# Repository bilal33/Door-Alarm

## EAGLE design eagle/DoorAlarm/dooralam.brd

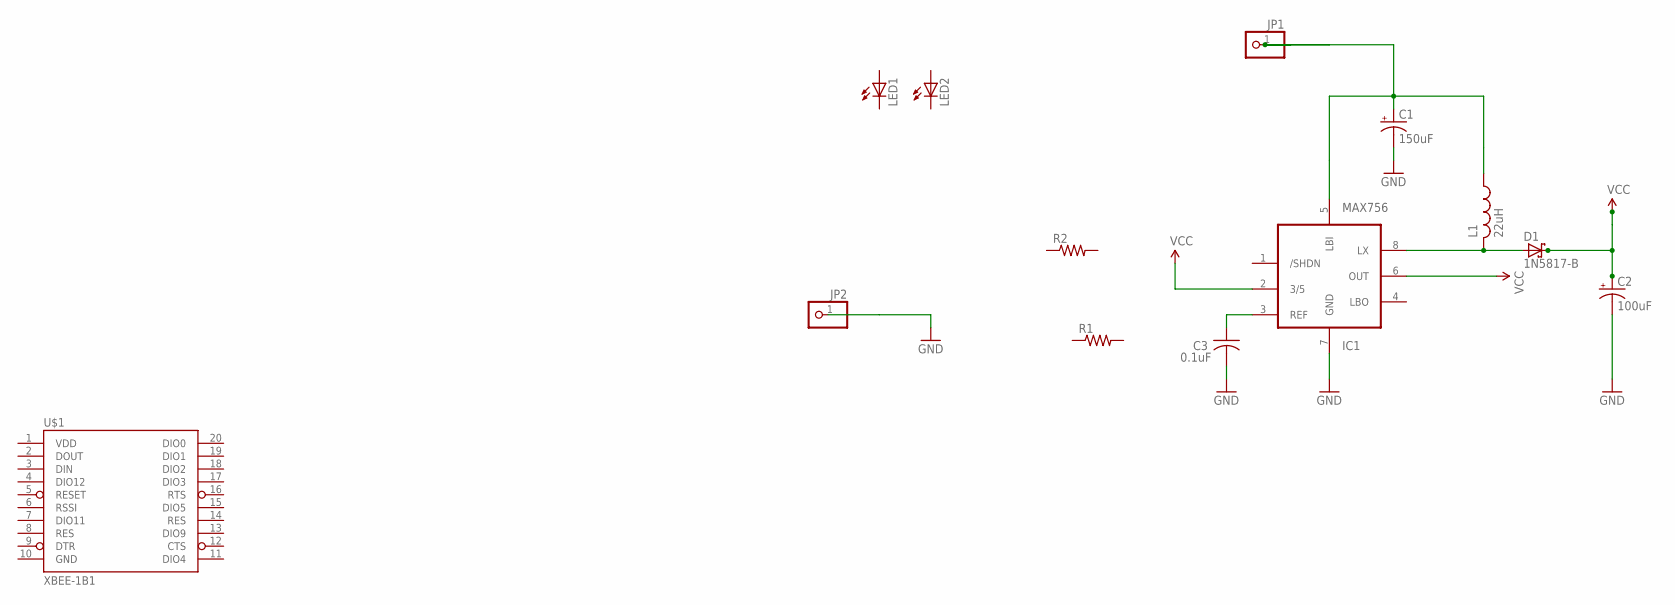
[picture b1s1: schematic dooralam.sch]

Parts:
C1: 150uF; E2-5
C2: 100uF; E2-5
C3: 0.1uF; C025-025X050
D1: 1N5817-B; DO41-7.6
IC1: MAX756; DIL08
JP1, JP2: PINHD-1X1; 1X01
L1: 22uH; 6000
LED1, LED2: LED3MM
R1, R2: R-US_0204/7; 0204/7
U$1: XBEE-1B1; XBEE-1

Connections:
BATT+: C1.+, IC1.5 (LBI), JP1.1, L1.1
GND: C1.-, C2.-, C3.2, IC1.7 (GND), JP2.1, U$1.10 (GND)
LX: D1.A, IC1.8 (LX), L1.2
unnamed: C3.1, IC1.3 (REF)
VCC: C2.+, D1.C, IC1.2 (3/5), IC1.6 (OUT)
VDD: U$1.1 (VDD)

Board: 2 copper layers, 13 parts (0 on the bottom side), 5 nets, no tracks yet.

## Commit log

2011-12-30 first check in for the door alarm
2011-12-31 still need to add parts for low battery detection, but power supply is donw

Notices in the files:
parts and their libraries:
SparkFun: Licensing: CC v3.0 Share-Alike You are welcome to use this library for commercial purposes.
